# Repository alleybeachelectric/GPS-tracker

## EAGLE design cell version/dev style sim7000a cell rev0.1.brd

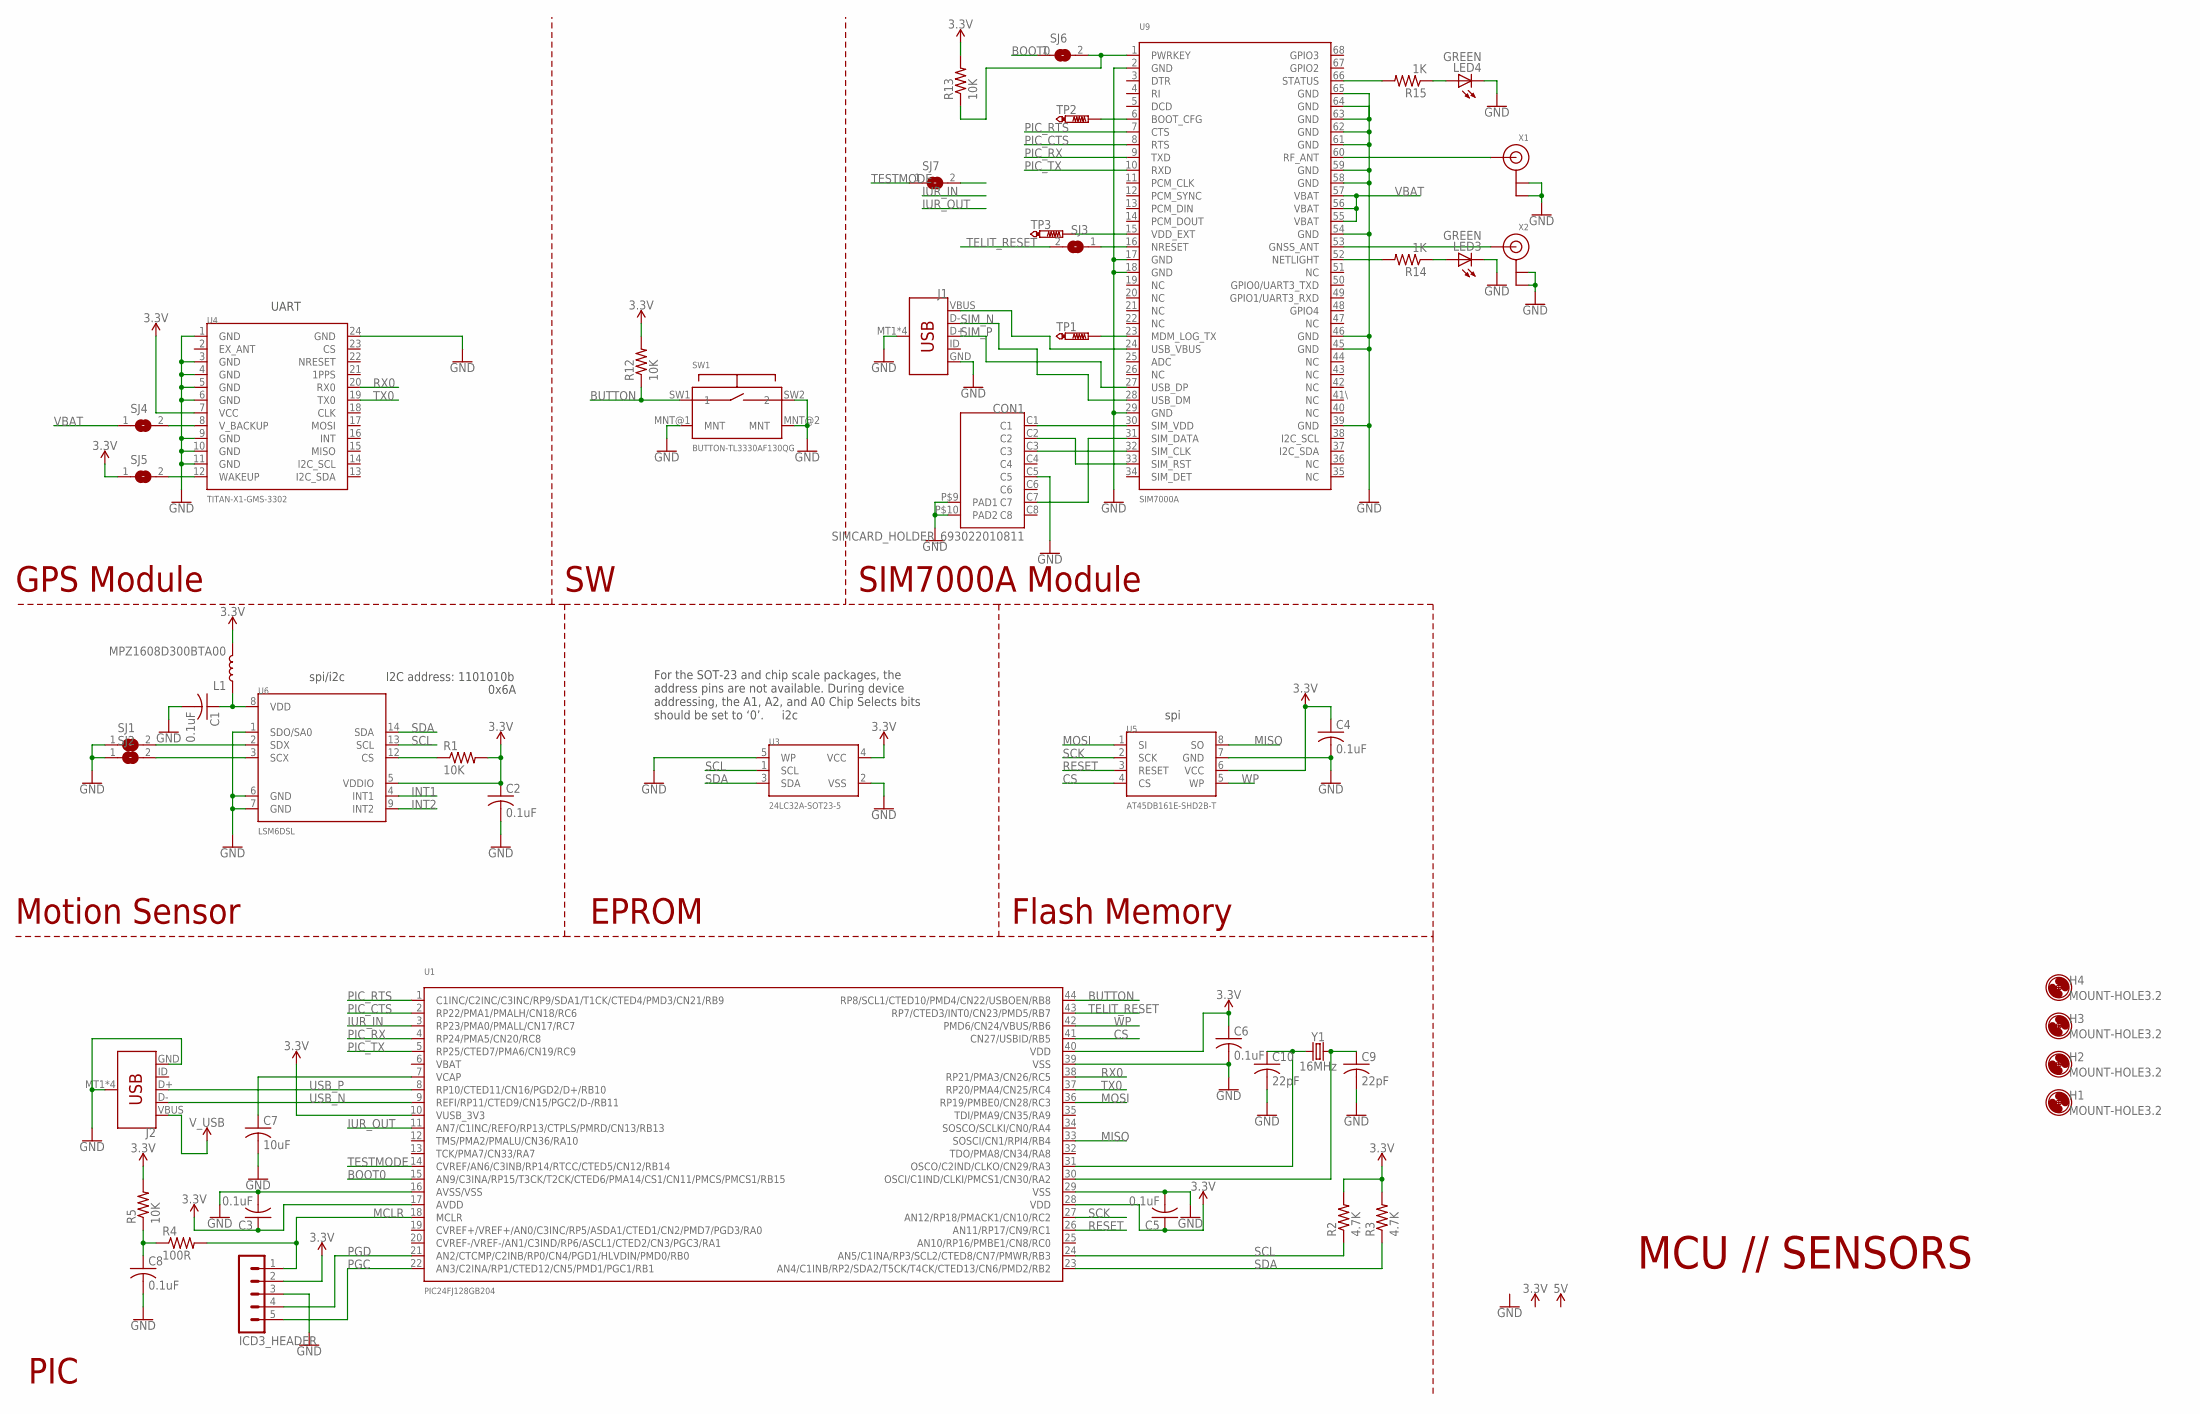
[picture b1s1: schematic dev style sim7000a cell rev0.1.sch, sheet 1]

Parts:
C1, C2, C3, C4, C5, C6, C8: 0.1uF; C0402
C7: 10uF; C0603
C9, C10: 22pF; C0402
CON1: SIMCARD_HOLDER_693022010811
H1, H2, H3, H4: MOUNT-HOLE3.2; 3,2
ICD3_HEADER: MA05-1
J1, J2: USB_MICRO-B_SMT; USB-MICROB
L1: MPZ1608D300BTA00; 0402
LED3, LED4: GREEN; CHIP-LED0603
R1, R5, R12, R13: 10K; R0402
R2, R3: 4.7K; R0402
R4: 100R; R0402
R14, R15: 1K; R0402
SJ1, SJ2, SJ3, SJ4, SJ5, SJ6, SJ7: SJ
SW1: BUTTON-TL3330AF130QG
TP1, TP2, TP3: PTR1PAD1-17; P1-17
U1: PIC24FJ128GB204
U3: 24LC32A-SOT23-5
U4: TITAN-X1-GMS-3302
U5: AT45DB161E-SHD2B-T
U6: LSM6DSL
U9: SIM7000A
U$1, U$2, U$3, U$4: FIDUCIAL; FIDUCIAL_1MM
X1, X2: ANTENNA_U.FL; U.FL
Y1: 16MHz; CRYSTAL-SMD-5X3.2-4PAD

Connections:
3.3V: C2.1, C3.1, C4.1, C5.1, C6.1, ICD3_HEADER.2, L1.2, R1.2, R2.2, R3.2, R5.2, R12.2, R13.2, SJ5.1, U1.10 (VUSB_3V3), U1.17 (AVDD), U1.28 (VDD), U1.40 (VDD), U3.4 (VCC), U4.7 (VCC), U5.6 (VCC), U6.5 (VDDIO); also elsewhere on the board
BOOT0: SJ6.1, U1.15 (AN9/C3INA/RP15/T3CK/T2CK/CTED6/PMA14/CS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)
BUTTON: R12.1, SW1.SW1 (1), U1.44 (RP8/SCL1/CTED10/PMD4/CN22/USBOEN/RB8)
CS: U1.41 (CN27/USBID/RB5), U5.4 (CS)
GND: C1.2, C2.2, C3.2, C4.2, C5.2, C6.2, C7.2, C8.2, C9.2, C10.2, CON1.C5, CON1.P$9 (PAD1), CON1.P$10 (PAD2), ICD3_HEADER.3, J1.GND, J1.MT1 (SHIELD), J1.MT2 (SHIELD), J1.P$1 (SHIELD), J1.P$2 (SHIELD), J2.GND, J2.MT1 (SHIELD), J2.MT2 (SHIELD), J2.P$1 (SHIELD), J2.P$2 (SHIELD), LED3.C, LED4.C, SJ1.1, SJ2.1, SW1.MNT@1 (MNT), SW1.MNT@2 (MNT), SW1.SW2 (2), U1.16 (AVSS/VSS), U1.29 (VSS), U1.39 (VSS), U3.2 (VSS), U3.5 (WP), U4.1 (GND), U4.3 (GND), U4.4 (GND), U4.5 (GND), U4.6 (GND), U4.9 (GND), U4.10 (GND), U4.11 (GND), U4.24 (GND), U5.7 (GND), U6.1 (SDO/SA0), U6.6 (GND), U6.7 (GND), U9.2 (GND), U9.17 (GND), U9.18 (GND), U9.29 (GND), U9.39 (GND), U9.45 (GND), U9.46 (GND), U9.54 (GND), U9.58 (GND), U9.59 (GND), U9.61 (GND), U9.62 (GND), U9.63 (GND), U9.64 (GND), U9.65 (GND), X1.1 (GND), X1.2 (GND), X2.1 (GND), X2.2 (GND); also elsewhere on the board
INT1: U6.4 (INT1)
INT2: U6.9 (INT2)
IUR_IN: U1.3 (RP23/PMA0/PMALL/CN17/RC7)
IUR_OUT: U1.11 (AN7/C1INC/REFO/RP13/CTPLS/PMRD/CN13/RB13)
MCLR: ICD3_HEADER.1, R4.2, U1.18 (MCLR)
MISO: U1.33 (SOSCI/CN1/RPI4/RB4), U5.8 (SO)
MOSI: U1.36 (RP19/PMBE0/CN28/RC3), U5.1 (SI)
unnamed: SJ1.2, U6.2 (SDX)
unnamed: SJ2.2, U6.3 (SCX)
unnamed: R1.1, U6.12 (CS)
unnamed: SJ4.2, U4.8 (V_BACKUP)
unnamed: C1.1, L1.1, U6.8 (VDD)
unnamed: C8.1, R4.1, R5.1
unnamed: C9.1, U1.30 (OSCI/C1IND/CLKI/PMCS1/CN30/RA2), Y1.3 (2)
unnamed: C10.1, U1.31 (OSCO/C2IND/CLKO/CN29/RA3), Y1.1
unnamed: C7.1, U1.7 (VCAP)
unnamed: SJ3.1, U9.16 (NRESET)
unnamed: R14.2, U9.52 (NETLIGHT)
unnamed: U9.60 (RF_ANT), X1.3 (SIGNAL)
unnamed: R13.1, SJ6.2, U9.1 (PWRKEY)
unnamed: CON1.C1, U9.30 (SIM_VDD)
unnamed: CON1.C3, U9.32 (SIM_CLK)
unnamed: CON1.C7, U9.31 (SIM_DATA)
unnamed: CON1.C2, U9.33 (SIM_RST)
unnamed: LED3.A, R14.1
unnamed: TP1.TP, U9.23 (MDM_LOG_TX)
unnamed: LED4.A, R15.1
unnamed: R15.2, U9.66 (STATUS)
unnamed: TP2.TP, U9.6 (BOOT_CFG)
unnamed: J1.VBUS, U9.24 (USB_VBUS)
unnamed: U9.53 (GNSS_ANT), X2.3 (SIGNAL)
unnamed: TP3.TP, U9.15 (VDD_EXT)
PGC: ICD3_HEADER.5, U1.22 (AN3/C2INA/RP1/CTED12/CN5/PMD1/PGC1/RB1)
PGD: ICD3_HEADER.4, U1.21 (AN2/CTCMP/C2INB/RP0/CN4/PGD1/HLVDIN/PMD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)
PIC_CTS: U1.2 (RP22/PMA1/PMALH/CN18/RC6), U9.8 (RTS)
PIC_RTS: U1.1 (C1INC/C2INC/C3INC/RP9/SDA1/T1CK/CTED4/P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), U9.7 (CTS)
PIC_RX: U1.4 (RP24/PMA5/CN20/RC8), U9.9 (TXD)
PIC_TX: U1.5 (RP25/CTED7/PMA6/CN19/RC9), U9.10 (RXD)
RESET: U1.26 (AN11/RP17/CN9/RC1), U5.3 (RESET)
RX0: U1.38 (RP21/PMA3/CN26/RC5), U4.20 (RX0)
SCK: U1.27 (AN12/RP18/PMACK1/CN10/RC2), U5.2 (SCK)
SCL: R2.1, U1.24 (AN5/C1INA/RP3/SCL2/CTED8/CN7/PMWR/RB3), U3.1 (SCL), U6.13 (SCL)
SDA: R3.1, U1.23 (AN4/C1INB/RP2/SDA2/T5CK/T4CK/CTED13/CN6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), U3.3 (SDA), U6.14 (SDA)
SIM_N: J1.D-, U9.28 (USB_DM)
SIM_P: J1.D+, U9.27 (USB_DP)
TELIT_RESET: SJ3.2, U1.43 (RP7/CTED3/INT0/CN23/PMD5/RB7)
TELIT_WAKEUP: SJ5.2, U4.12 (WAKEUP)
TESTMODE: SJ7.1, U1.14 (CVREF/AN6/C3INB/RP14/RTCC/CTED5/CN12/RB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)
TX0: U1.37 (RP20/PMA4/CN25/RC4), U4.19 (TX0)
USB_N: J2.D-, U1.9 (REFI/RP11/CTED9/CN15/PGC2/D-/RB11)
USB_P: J2.D+, U1.8 (RP10/CTED11/CN16/PGD2/D+/RB10)
VBAT: SJ4.1, U9.55 (VBAT), U9.56 (VBAT), U9.57 (VBAT); also elsewhere on the board
V_USB: J2.VBUS; also elsewhere on the board
WP: U1.42 (PMD6/CN24/VBUS/RB6), U5.5 (WP)

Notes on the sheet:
For the SOT-23 and chip scale packages, the address pins are not available. During device addressing, the A1, A2, and A0 Chip Selects bits should be set to ‘0’.
i2c
spi
spi/i2c
I2C address: 1101010b
0x6A
MCU // SENSORS
UART
GPS Module
SIM7000A Module
EPROM
PIC
Motion Sensor
Flash Memory

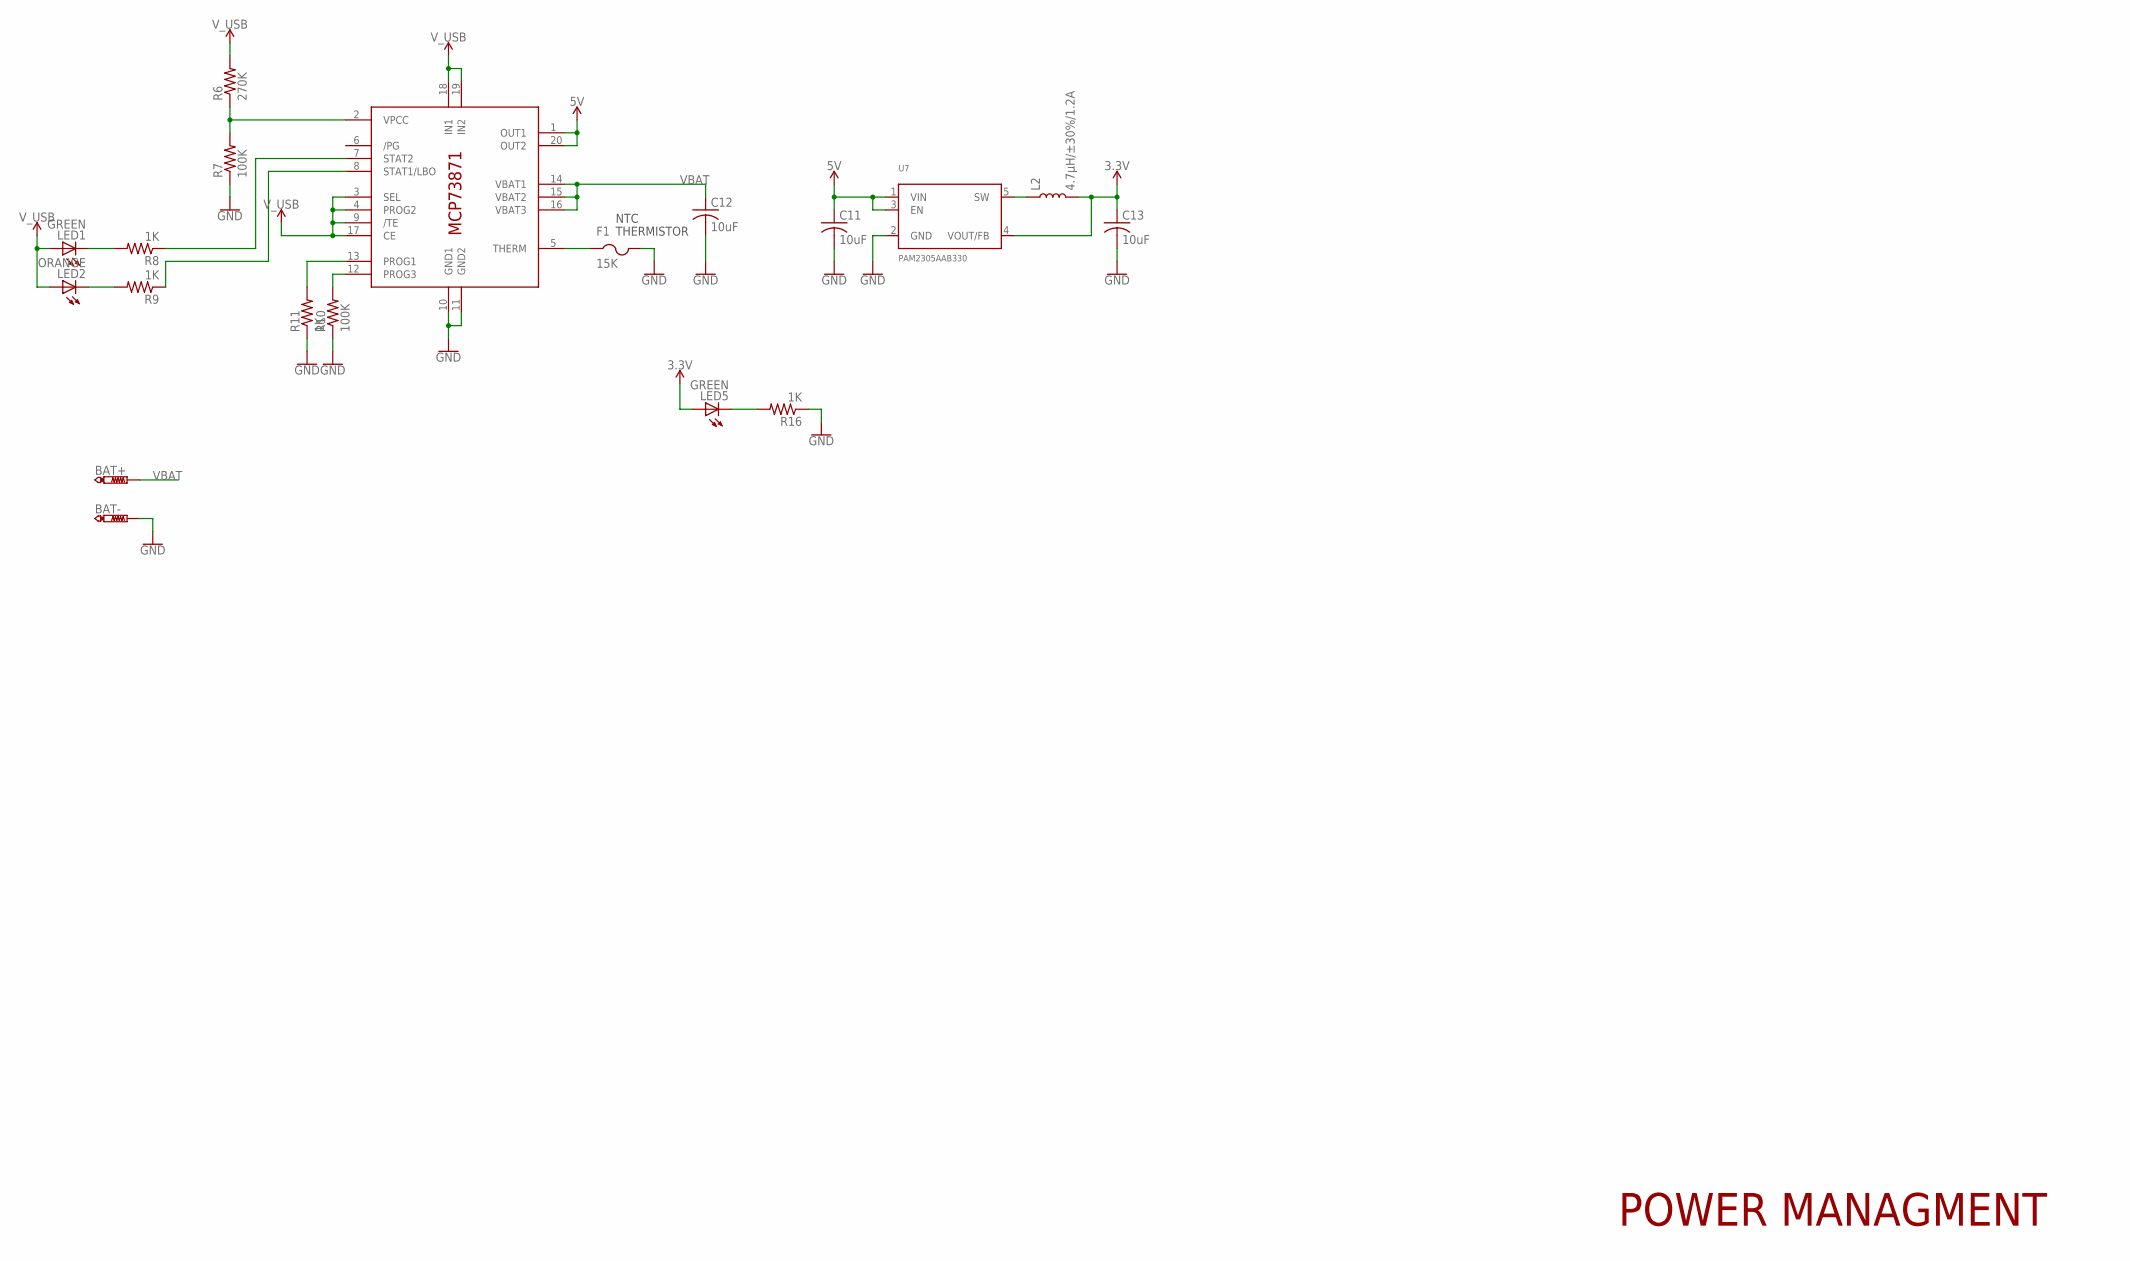
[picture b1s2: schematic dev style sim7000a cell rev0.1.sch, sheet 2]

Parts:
BAT+: PTR1B2,54; B2,54
BAT-: PTR1B2,54; B2,54
C11, C13: 10uF; C0805
C12: 10uF; C0603
F1: 15K; R1206
L2: 4.7µH/±30%/1.2A; INDUCTOR_4.7UH
LED1, LED5: GREEN; CHIP-LED0603
LED2: ORANGE; CHIP-LED0603
R6: 270K; R0402
R7, R10: 100K; R0402
R8, R9, R11, R16: 1K; R0402
U7: PAM2305AAB330
U8: MCP73871; QFN20

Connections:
3.3V: C13.1, L2.P$2 (2), LED5.A, U7.4 (VOUT/FB); also elsewhere on the board
5V: C11.1, U7.1 (VIN), U7.3 (EN), U8.1 (OUT1), U8.20 (OUT2)
GND: BAT-.TP, C11.2, C12.2, C13.2, F1.2, R7.1, R10.1, R11.1, R16.1, U7.2 (GND), U8.10 (GND1), U8.11 (GND2); also elsewhere on the board
unnamed: R6.1, R7.2, U8.2 (VPCC)
unnamed: LED1.C, R8.2
unnamed: LED2.C, R9.2
unnamed: R8.1, U8.7 (STAT2)
unnamed: R9.1, U8.8 (STAT1/LBO)
unnamed: L2.P$1 (1), U7.5 (SW)
unnamed: R10.2, U8.12 (PROG3)
unnamed: R11.2, U8.13 (PROG1)
unnamed: F1.1, U8.5 (THERM)
unnamed: LED5.C, R16.2
VBAT: BAT+.TP, C12.1, U8.14 (VBAT1), U8.15 (VBAT2), U8.16 (VBAT3); also elsewhere on the board
V_USB: LED1.A, LED2.A, R6.2, U8.3 (SEL), U8.4 (PROG2), U8.9 (/TE), U8.17 (CE), U8.18 (IN1), U8.19 (IN2); also elsewhere on the board

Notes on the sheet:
THERMISTOR
NTC
POWER MANAGMENT

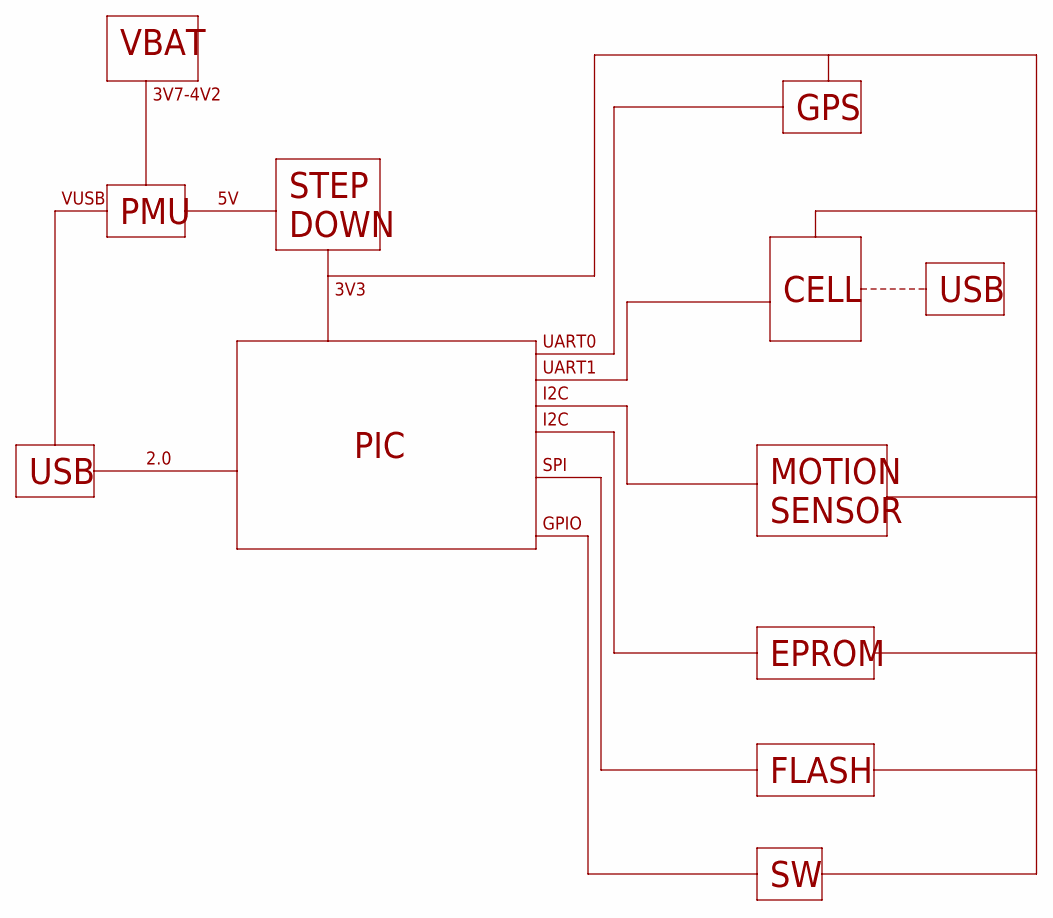
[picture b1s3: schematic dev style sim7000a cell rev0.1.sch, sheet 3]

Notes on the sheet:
PIC
GPS
CELL
MOTION SENSOR
EPROM
FLASH
PMU
USB
VBAT
STEP DOWN
VUSB
3V7-4V2
3V3
UART0
UART1
I2C
SPI
GPIO
2.0

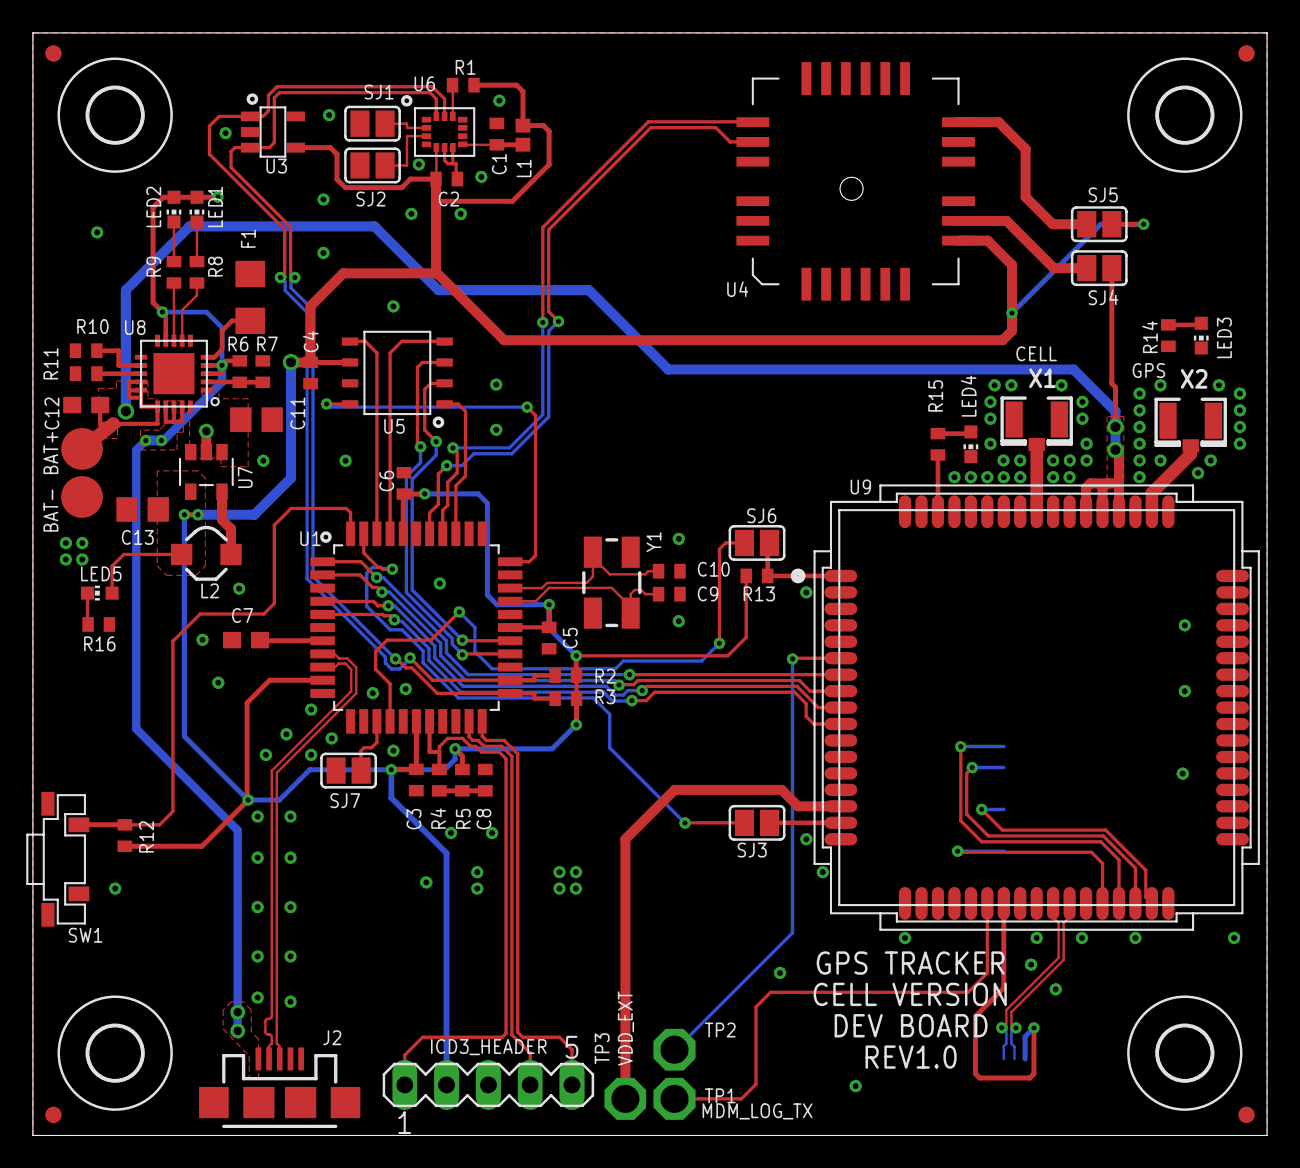
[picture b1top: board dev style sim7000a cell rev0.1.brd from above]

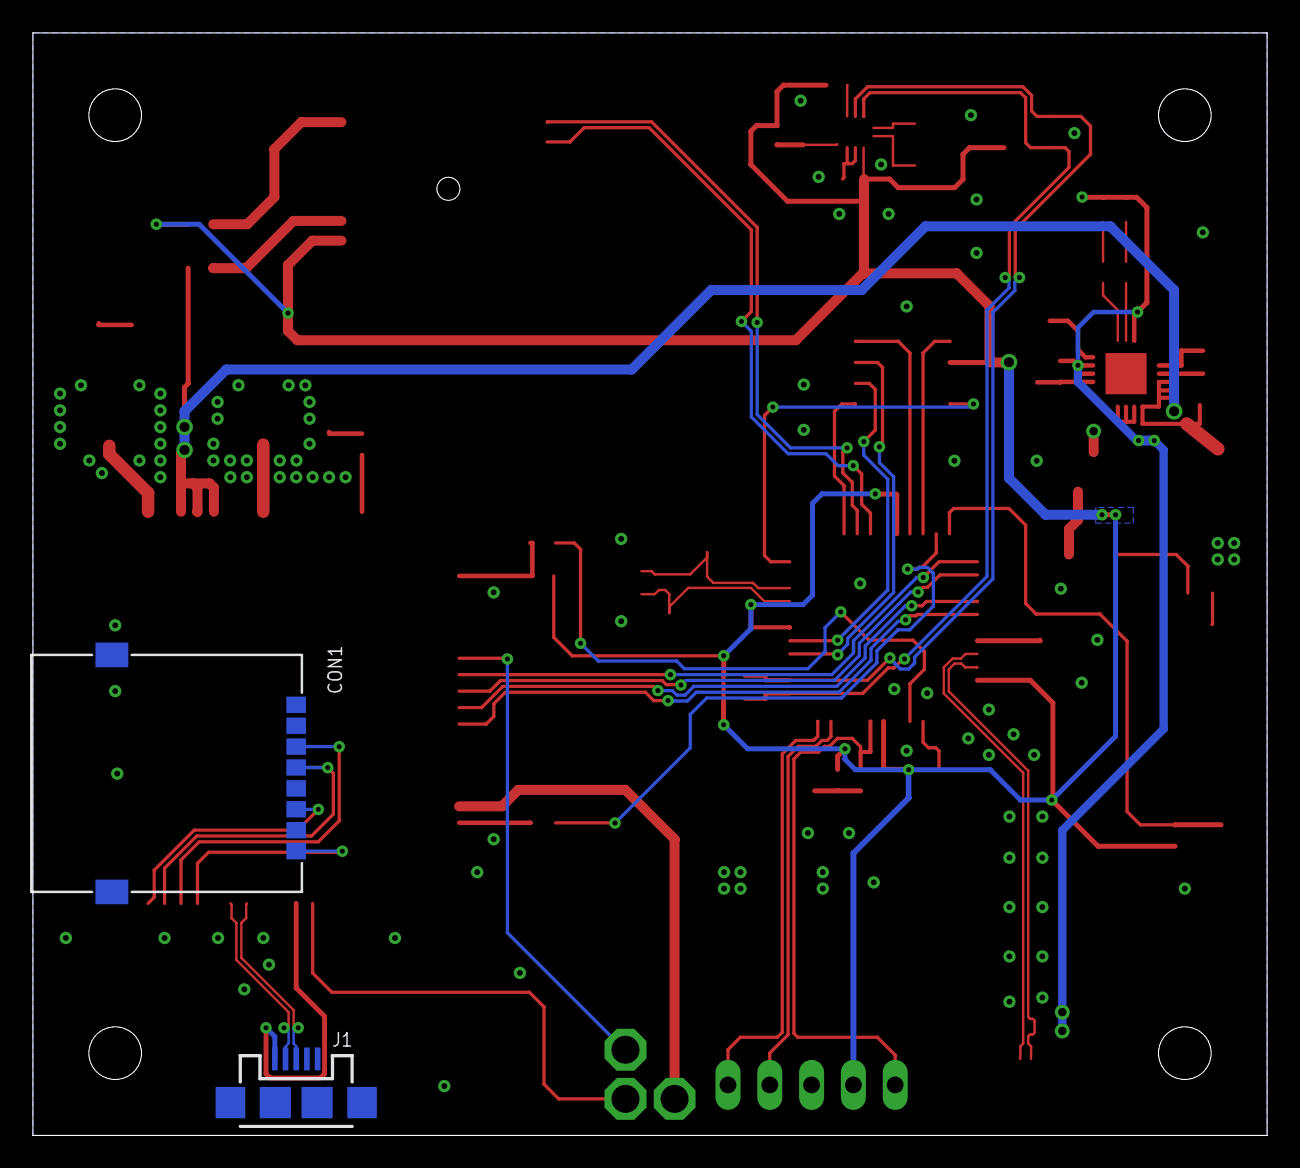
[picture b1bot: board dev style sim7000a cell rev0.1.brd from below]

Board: 2 copper layers, 75.0 x 67.0 mm, 73 parts (2 on the bottom side), 66 nets.

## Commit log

2017-11-21 start
2017-11-22 made parts!
2017-11-23 added bat management
2017-11-27 reroute with new component placements
    had a redo on the component placement for better routability, changed the battery charging circuit, still need to confirm which pins for communications go to the PIC. need to still add button.
2017-12-07 routed for PIC for cleaner routing
2017-12-19 starting a dev style board to work with first.
2017-12-21 added all power routing for the lora version. need to clean up folder/organize it.
    Everything is routed. need to get approval with second pair of eyes.
2018-01-14 updated cell dev
2018-01-15 added antennas and fiducials, finished routing, cleaned silk, added custom silk
2018-03-08 pushed after a while

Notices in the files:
parts and their libraries:
SparkFun-Connectors: Licensing: Creative Commons ShareAlike 4.0 International - https://creativecommons.org/licenses/by-sa/4.0
